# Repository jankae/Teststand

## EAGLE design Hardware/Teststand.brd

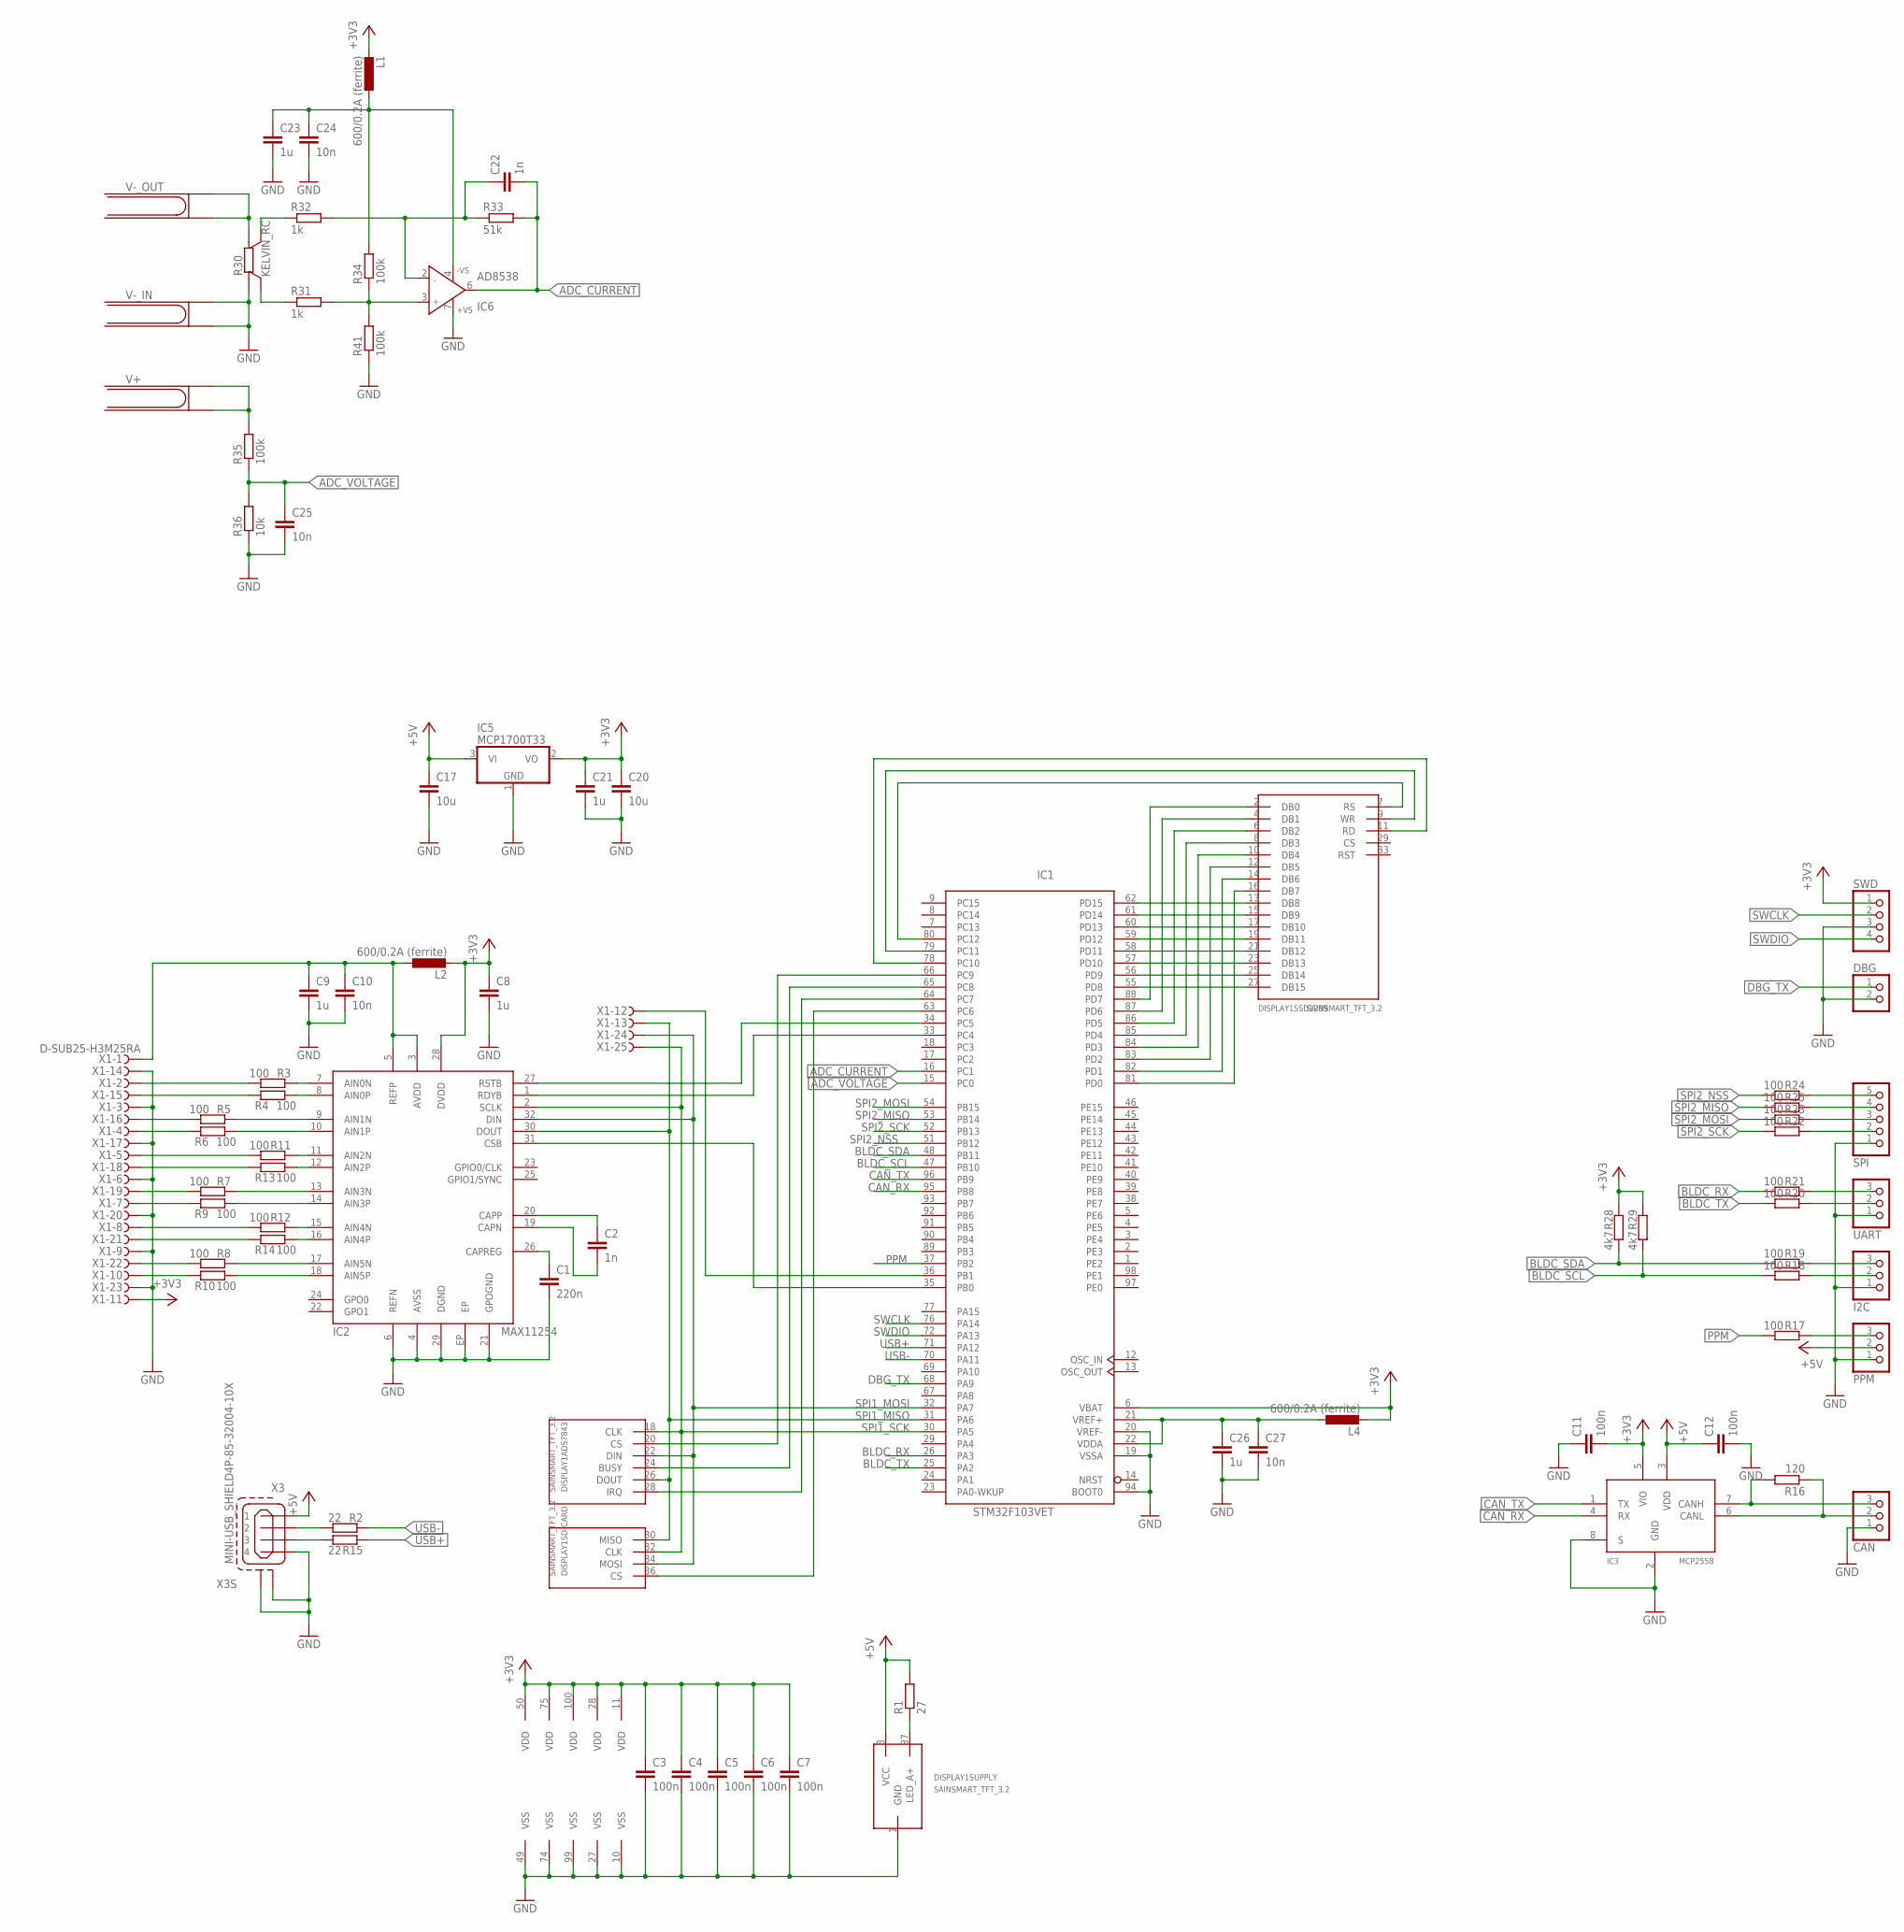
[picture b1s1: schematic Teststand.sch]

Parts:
C1: 220n; C0603K
C2, C22: 1n; C0603K
C3, C4, C5, C6, C7, C11, C12: 100n; C0603K
C8, C9, C23, C26: 1u; C0603K
C10, C24, C25, C27: 10n; C0603K
C17, C20: 10u; C1206
C21: 1u; C1206
CAN: PINHD-1X3/90; 1X03/90
DBG: PINHD-1X2; 1X02
DISPLAY1: SAINSMART_TFT_3.2
I2C: PINHD-1X3/90; 1X03/90
IC1: STM32F103VET; LQFP100
IC2: MAX11254; TQFP32-EP
IC3: MCP2558; SOIC8
IC5: MCP1700T33; SOT23
IC6: AD8538; SO8
L1, L2, L4: 600/0.2A (ferrite); L2012C
PPM: PINHD-1X3/90; 1X03/90
R1: 27; M1206
R2, R15: 22; R0603
R3, R4, R5, R6, R7, R8, R9, R10, R11, R12, R13, R14, R17, R18, R19, R20, R21, R22, R23, R24, R25: 100; R0603
R16: 120; R0603
R28, R29: 4k7; R0603
R30: KELVIN_RC; CST0612
R31, R32: 1k; R0603
R33: 51k; R0603
R34, R35, R41: 100k; R0603
R36: 10k; R0603
SPI: PINHD-1X5/90; 1X05/90
SWD: PINHD-1X4; 1X04
UART: PINHD-1X3/90; 1X03/90
V+: 4MMJACK
V-_IN: 4MMJACK
V-_OUT: 4MMJACK
X1: D-SUB25-H3M25RA; H3M25RA
X3: MINI-USB_SHIELD4P-85-32004-10X; 85-32004-10X

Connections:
+3V3: C3.1, C4.1, C5.1, C6.1, C7.1, C8.1, C11.2, C20.1, C21.1, IC1.6 (VBAT), IC1.11 (VDD), IC1.28 (VDD), IC1.50 (VDD), IC1.75 (VDD), IC1.100 (VDD), IC2.28 (DVDD), IC3.5 (VIO), IC5.2 (VO), L1.2, L2.2, L4.2, R28.1, R29.1, SWD.1, X1.11
+5V: C12.1, C17.1, DISPLAY1.3 (VCC), IC3.3 (VDD), IC5.3 (VI), PPM.2, R1.2, X3.1
ADC_CURRENT: C22.2, IC1.16 (PC1), IC6.6 (OUT), R33.2
ADC_VOLTAGE: C25.1, IC1.15 (PC0), R35.1, R36.2
BLDC_RX: IC1.26 (PA3), R21.2
BLDC_SCL: IC1.47 (PB10), R18.2, R29.2
BLDC_SDA: IC1.48 (PB11), R19.2, R28.2
BLDC_TX: IC1.25 (PA2), R20.2
CAN_RX: IC1.95 (PB8), IC3.4 (RX)
CAN_TX: IC1.96 (PB9), IC3.1 (TX)
DBG_TX: DBG.1, IC1.68 (PA9)
GND: C1.2, C3.2, C4.2, C5.2, C6.2, C7.2, C8.2, C9.2, C10.2, C11.1, C12.2, C17.2, C20.2, C21.2, C23.2, C24.2, C25.2, C26.2, C27.2, CAN.1, DBG.2, DISPLAY1.1 (GND), I2C.1, IC1.10 (VSS), IC1.19 (VSSA), IC1.20 (VREF-), IC1.27 (VSS), IC1.49 (VSS), IC1.74 (VSS), IC1.94 (BOOT0), IC1.99 (VSS), IC2.4 (AVSS), IC2.6 (REFN), IC2.21 (GPOGND), IC2.29 (DGND), IC2.EP, IC3.2 (GND), IC3.8 (S), IC5.1 (GND), IC6.7 (+VS), PPM.1, R30.B, R36.1, R41.1, SPI.1, SWD.3, UART.1, V-_IN.1@1 (1), V-_IN.1@2 (2), X1.3, X1.6, X1.9, X1.14, X1.17, X1.20, X1.23, X3.4, X3.M1 (S1), X3.M2 (S2)
unnamed: DISPLAY1.13 (DB8), IC1.62 (PD15)
unnamed: DISPLAY1.15 (DB9), IC1.61 (PD14)
unnamed: DISPLAY1.17 (DB10), IC1.60 (PD13)
unnamed: DISPLAY1.19 (DB11), IC1.59 (PD12)
unnamed: DISPLAY1.21 (DB12), IC1.58 (PD11)
unnamed: DISPLAY1.23 (DB13), IC1.57 (PD10)
unnamed: DISPLAY1.25 (DB14), IC1.56 (PD9)
unnamed: DISPLAY1.27 (DB15), IC1.55 (PD8)
unnamed: DISPLAY1.2 (DB0), IC1.88 (PD7)
unnamed: DISPLAY1.4 (DB1), IC1.87 (PD6)
unnamed: DISPLAY1.6 (DB2), IC1.86 (PD5)
unnamed: DISPLAY1.8 (DB3), IC1.85 (PD4)
unnamed: DISPLAY1.10 (DB4), IC1.84 (PD3)
unnamed: DISPLAY1.12 (DB5), IC1.83 (PD2)
unnamed: DISPLAY1.14 (DB6), IC1.82 (PD1)
unnamed: DISPLAY1.16 (DB7), IC1.81 (PD0)
unnamed: DISPLAY1.7 (RS), IC1.80 (PC12)
unnamed: DISPLAY1.9 (WR), IC1.79 (PC11)
unnamed: DISPLAY1.11 (RD), IC1.78 (PC10)
unnamed: DISPLAY1.20 (CS), IC1.66 (PC9)
unnamed: DISPLAY1.24 (BUSY), IC1.65 (PC8)
unnamed: C1.1, IC2.26 (CAPREG)
unnamed: C2.1, IC2.20 (CAPP)
unnamed: C2.2, IC2.19 (CAPN)
unnamed: R3.2, X1.2
unnamed: R4.1, X1.15
unnamed: DISPLAY1.37 (LED_A+), R1.1
unnamed: C9.1, C10.1, IC2.3 (AVDD), IC2.5 (REFP), L2.1, X1.1
unnamed: IC2.9 (AIN1N), R5.1
unnamed: IC2.10 (AIN1P), R6.2
unnamed: R5.2, X1.16
unnamed: R6.1, X1.4
unnamed: IC2.13 (AIN3N), R7.1
unnamed: IC2.14 (AIN3P), R9.2
unnamed: R11.2, X1.5
unnamed: R13.1, X1.18
unnamed: IC2.17 (AIN5N), R8.1
unnamed: IC2.18 (AIN5P), R10.2
unnamed: R7.2, X1.19
unnamed: R9.1, X1.7
unnamed: R12.2, X1.8
unnamed: R14.1, X1.21
unnamed: IC2.15 (AIN4N), R12.1
unnamed: IC2.16 (AIN4P), R14.2
unnamed: IC2.12 (AIN2P), R13.2
unnamed: IC2.11 (AIN2N), R11.1
unnamed: R8.2, X1.22
unnamed: R10.1, X1.10
unnamed: IC2.8 (AIN0P), R4.2
unnamed: IC2.7 (AIN0N), R3.1
unnamed: R2.2, X3.2
unnamed: R15.2, X3.3
unnamed: CAN.3, IC3.7 (CANH), R16.2
unnamed: CAN.2, IC3.6 (CANL), R16.1
unnamed: IC1.34 (PC5), IC2.27 (RSTB)
unnamed: R24.1, SPI.5
unnamed: R25.1, SPI.4
unnamed: R23.1, SPI.3
unnamed: R22.1, SPI.2
unnamed: R21.1, UART.3
unnamed: R20.1, UART.2
unnamed: I2C.3, R19.1
unnamed: I2C.2, R18.1
unnamed: PPM.3, R17.1
unnamed: IC1.33 (PC4), IC2.1 (RDYB)
unnamed: IC1.35 (PB0), IC2.31 (CSB)
unnamed: DISPLAY1.28 (IRQ), IC1.64 (PC7)
unnamed: DISPLAY1.36 (CS), IC1.63 (PC6)
unnamed: IC1.36 (PB1), X1.12
unnamed: R35.2, V+.1@1 (1), V+.1@2 (2)
unnamed: R30.A, V-_OUT.1@1 (1), V-_OUT.1@2 (2)
unnamed: C26.1, C27.1, IC1.21 (VREF+), IC1.22 (VDDA), L4.1
unnamed: C23.1, C24.1, IC6.4 (-VS), L1.1, R34.2
unnamed: R30.SA, R32.1
unnamed: C22.1, IC6.2 (IN-), R32.2, R33.1
unnamed: R30.SB, R31.1
unnamed: IC6.3 (IN+), R31.2, R34.1, R41.2
PPM: IC1.37 (PB2), R17.2
SPI1_MISO: DISPLAY1.26 (DOUT), DISPLAY1.30 (MISO), IC1.31 (PA6), IC2.30 (DOUT), X1.13
SPI1_MOSI: DISPLAY1.22 (DIN), DISPLAY1.34 (MOSI), IC1.32 (PA7), IC2.32 (DIN), X1.24
SPI1_SCK: DISPLAY1.18 (CLK), DISPLAY1.32 (CLK), IC1.30 (PA5), IC2.2 (SCLK), X1.25
SPI2_MISO: IC1.53 (PB14), R25.2
SPI2_MOSI: IC1.54 (PB15), R23.2
SPI2_NSS: IC1.51 (PB12), R24.2
SPI2_SCK: IC1.52 (PB13), R22.2
SWCLK: IC1.76 (PA14), SWD.2
SWDIO: IC1.72 (PA13), SWD.4
USB+: IC1.71 (PA12), R15.1
USB-: IC1.70 (PA11), R2.1

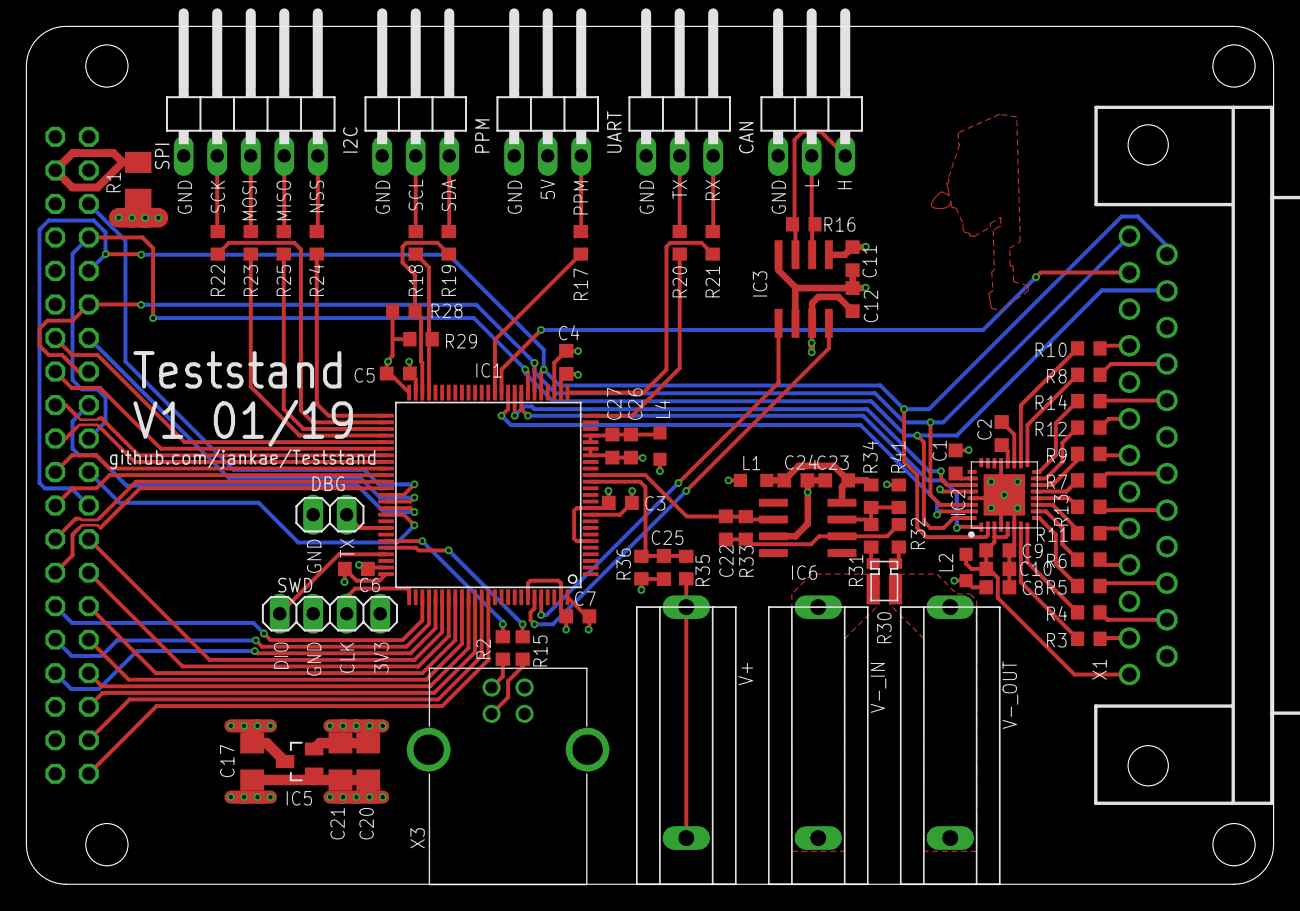
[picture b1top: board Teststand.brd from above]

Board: 4 copper layers, 94.5 x 65.0 mm, 77 parts (1 on the bottom side), 101 nets.

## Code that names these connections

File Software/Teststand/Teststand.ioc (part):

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Mcu.Name=STM32F103V(C-D-E)Tx
Mcu.Package=LQFP100
Mcu.UserName=STM32F103VETx
PA10.Mode=Asynchronous
PA10.Signal=USART1_RX
PA11.Mode=Device
PA11.Signal=USB_DM
PA12.Mode=Device
PA12.Signal=USB_DP
PA13.Mode=Serial_Wire
PA13.Signal=SYS_JTMS-SWDIO
PA14.Mode=Serial_Wire
PA14.Signal=SYS_JTCK-SWCLK
PA2.Mode=Asynchronous
PA2.Signal=USART2_TX
PA3.Mode=Asynchronous
PA3.Signal=USART2_RX
PA5.Mode=Full_Duplex_Master
PA5.Signal=SPI1_SCK
PA6.GPIOParameters=GPIO_PuPd
PA6.GPIO_PuPd=GPIO_PULLUP
PA6.Mode=Full_Duplex_Master
PA6.Signal=SPI1_MISO
PA7.Mode=Full_Duplex_Master
PA7.Signal=SPI1_MOSI
PA9.Mode=Asynchronous
PA9.Signal=USART1_TX
PB10.Mode=I2C
PB10.Signal=I2C2_SCL
PB11.Mode=I2C
PB11.Signal=I2C2_SDA
PB12.GPIOParameters=GPIO_Speed,GPIO_Label
PB12.GPIO_Label=SPI2_NSS
PB12.GPIO_Speed=GPIO_SPEED_FREQ_HIGH
PB12.Signal=GPIO_Output
PB13.Mode=Full_Duplex_Master
PB13.Signal=SPI2_SCK
PB14.Mode=Full_Duplex_Master
PB14.Signal=SPI2_MISO
PB15.Mode=Full_Duplex_Master
PB15.Signal=SPI2_MOSI
PB2.GPIOParameters=GPIO_Speed,GPIO_Label
PB2.GPIO_Label=PPM
PB2.GPIO_Speed=GPIO_SPEED_FREQ_HIGH
PB2.Signal=GPIO_Output
PB8.Mode=Master
PB8.Signal=CAN_RX
PB9.Mode=Master
PB9.Signal=CAN_TX
PC0.Signal=ADCx_IN10
PC1.Signal=ADCx_IN11
PC10.GPIOParameters=GPIO_Speed,GPIO_Label
PC10.GPIO_Label=DISPLAY_RD
PC10.GPIO_Speed=GPIO_SPEED_FREQ_HIGH
PC10.Signal=GPIO_Output
PC11.GPIOParameters=GPIO_Speed,GPIO_Label
PC11.GPIO_Label=DISPLAY_WR
PC11.GPIO_Speed=GPIO_SPEED_FREQ_HIGH
PC11.Signal=GPIO_Output
PC12.GPIOParameters=GPIO_Speed,GPIO_Label
PC12.GPIO_Label=DISPLAY_RS
PC12.GPIO_Speed=GPIO_SPEED_FREQ_HIGH
PC12.Signal=GPIO_Output
PC5.GPIOParameters=GPIO_Speed,GPIO_Label
PC5.GPIO_Label=MAX11254_RESET
PC5.GPIO_Speed=GPIO_SPEED_FREQ_HIGH
PC5.Signal=GPIO_Output
PC6.GPIOParameters=GPIO_Speed,PinState,GPIO_Label
PC6.GPIO_Label=SD_CS
PC6.GPIO_Speed=GPIO_SPEED_FREQ_HIGH
PC6.PinState=GPIO_PIN_SET
PC6.Signal=GPIO_Output
PC7.GPIOParameters=GPIO_Label
PC7.GPIO_Label=TOUCH_IRQ
PC7.Signal=GPIO_Input
PC8.GPIOParameters=GPIO_Label
PC8.GPIO_Label=TOUCH_BUSY
PC8.Signal=GPIO_Input
PC9.GPIOParameters=GPIO_Speed,PinState,GPIO_Label
PC9.GPIO_Label=TOUCH_CS
PC9.GPIO_Speed=GPIO_SPEED_FREQ_HIGH
PC9.PinState=GPIO_PIN_SET
PC9.Signal=GPIO_Output
PD0.GPIOParameters=GPIO_Speed
PD0.GPIO_Speed=GPIO_SPEED_FREQ_HIGH
PD0.Signal=GPIO_Output
PD1.GPIOParameters=GPIO_Speed
PD1.GPIO_Speed=GPIO_SPEED_FREQ_HIGH
PD1.Signal=GPIO_Output
PD10.GPIOParameters=GPIO_Speed
PD10.GPIO_Speed=GPIO_SPEED_FREQ_HIGH
PD10.Signal=GPIO_Output
PD11.GPIOParameters=GPIO_Speed
PD11.GPIO_Speed=GPIO_SPEED_FREQ_HIGH
PD11.Signal=GPIO_Output
PD12.GPIOParameters=GPIO_Speed
PD12.GPIO_Speed=GPIO_SPEED_FREQ_HIGH
PD12.Signal=GPIO_Output
PD13.GPIOParameters=GPIO_Speed
PD13.GPIO_Speed=GPIO_SPEED_FREQ_HIGH
PD13.Signal=GPIO_Output
PD14.GPIOParameters=GPIO_Speed
PD14.GPIO_Speed=GPIO_SPEED_FREQ_HIGH
PD14.Signal=GPIO_Output
PD15.GPIOParameters=GPIO_Speed
PD15.GPIO_Speed=GPIO_SPEED_FREQ_HIGH
PD15.Signal=GPIO_Output
PD2.GPIOParameters=GPIO_Speed
PD2.GPIO_Speed=GPIO_SPEED_FREQ_HIGH
PD2.Signal=GPIO_Output
PD3.GPIOParameters=GPIO_Speed
PD3.GPIO_Speed=GPIO_SPEED_FREQ_HIGH
PD3.Signal=GPIO_Output
PD4.GPIOParameters=GPIO_Speed
PD4.GPIO_Speed=GPIO_SPEED_FREQ_HIGH
PD4.Signal=GPIO_Output
PD5.GPIOParameters=GPIO_Speed
PD5.GPIO_Speed=GPIO_SPEED_FREQ_HIGH
PD5.Signal=GPIO_Output
PD6.GPIOParameters=GPIO_Speed
PD6.GPIO_Speed=GPIO_SPEED_FREQ_HIGH
PD6.Signal=GPIO_Output
PD7.GPIOParameters=GPIO_Speed
PD7.GPIO_Speed=GPIO_SPEED_FREQ_HIGH
PD7.Signal=GPIO_Output
PD8.GPIOParameters=GPIO_Speed
PD8.GPIO_Speed=GPIO_SPEED_FREQ_HIGH
PD8.Signal=GPIO_Output
PD9.GPIOParameters=GPIO_Speed
PD9.GPIO_Speed=GPIO_SPEED_FREQ_HIGH
PD9.Signal=GPIO_Output
PE13.GPIOParameters=GPIO_Speed,GPIO_Label
PE13.GPIO_Label=DISPLAY_CS
PE13.GPIO_Speed=GPIO_SPEED_FREQ_HIGH
PE13.Signal=GPIO_Output
PE8.GPIOParameters=GPIO_Speed,GPIO_Label
PE8.GPIO_Label=DISPLAY_RST
PE8.GPIO_Speed=GPIO_SPEED_FREQ_HIGH
PE8.Signal=GPIO_Output
RCC.SYSCLKFreq_VALUE=48000000
RCC.SYSCLKSource=RCC_SYSCLKSOURCE_PLLCLK
board=Teststand

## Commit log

2018-12-13 Partial schematic + layout
2019-01-25 MAX11254, display and touch driver + basic selftest
2019-01-25 BOM, Gerber + PCB art
2019-01-25 Description of PCB errors
2019-01-27 GUI adapted to purely touch based device
2019-01-28 FatFs support + loadcell driver
2019-01-29 Loadcell settings screen, removed 'selected' flag
2019-01-30 Loadcell calibration + value input dialog
2019-02-05 Touch calibration read/write, loadcell settigns improved
2019-02-06 Partial PPM motor driver
2019-02-07 Partial motor driver app + GUI improvements (better callbacks + radiobuttons)
2019-02-08 Slider added to driver control
2019-02-10 PPM driver completed, bugfix partial string display
2019-02-10 Bugfix touch input while switching apps
2019-02-10 BLCtrl driver stubs + support for Hex input
2019-02-10 I2C function support for BL-Ctrl
2019-02-12 BLDriver added (only percentage control so far)
2019-02-17 Configuration file handling
2019-02-18 Readback and display of motor driver data
2019-06-18 Combining loadcells to torque/thrust, preparations for ramp, general bugfixes
2019-06-18 Drawings top/bottom case
2019-06-20 Ramp execution
2019-06-21 Config improvements
2019-06-21 bugfixes
2019-07-10 Store sample rate of loadcells in config
2019-07-10 Add readback data to file when running test
